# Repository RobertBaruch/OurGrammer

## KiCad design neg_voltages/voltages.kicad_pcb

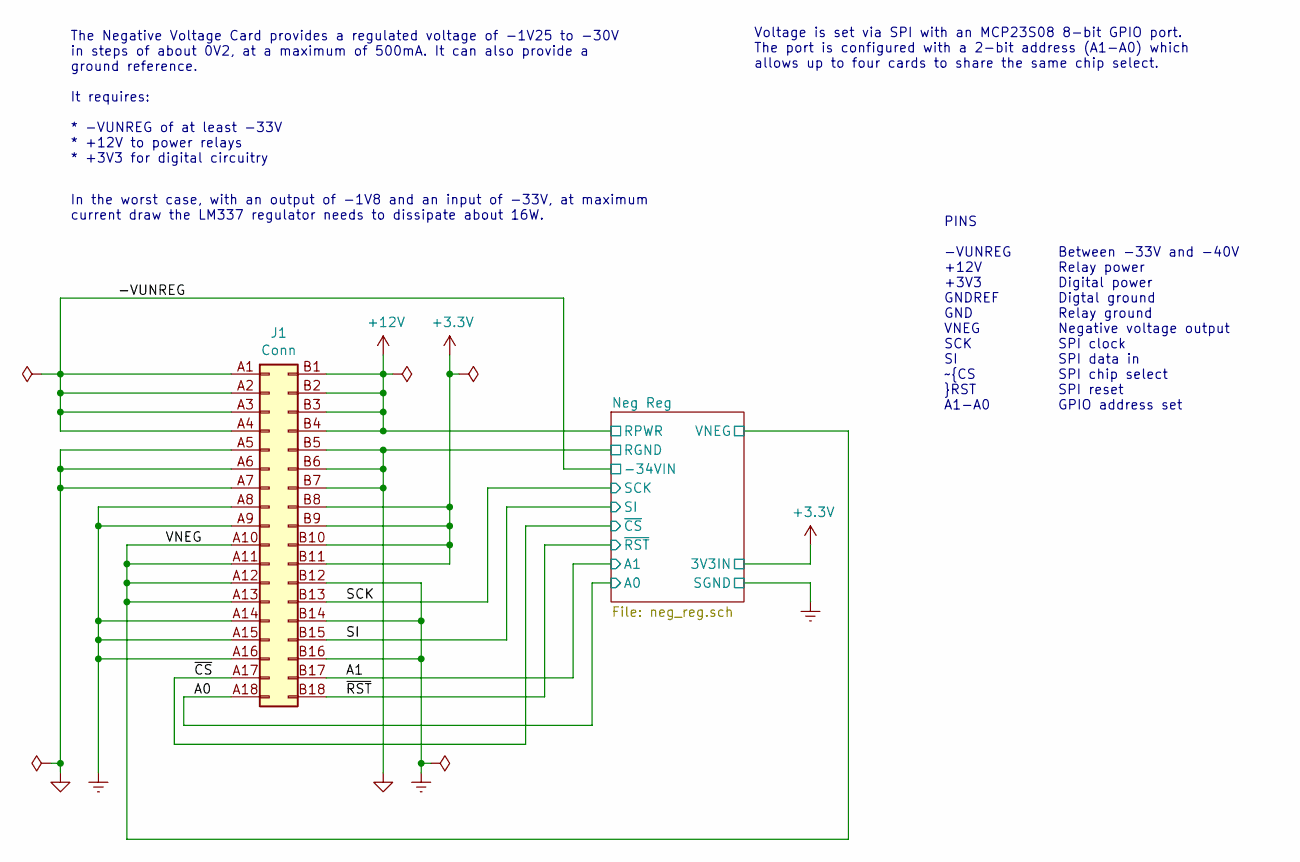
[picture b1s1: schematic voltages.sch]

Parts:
J1: Conn; BUS_PCIexpress_x1

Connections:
+3V3: J1.B8 (Pin_b8), J1.B9 (Pin_b9), J1.B10 (Pin_b10), J1.B11 (Pin_b11); also elsewhere on the board
+12V: J1.B1 (Pin_b1), J1.B2 (Pin_b2), J1.B3 (Pin_b3), J1.B4 (Pin_b4); also elsewhere on the board
/-VUNREG: J1.A1 (Pin_a1), J1.A2 (Pin_a2), J1.A3 (Pin_a3), J1.A4 (Pin_a4); also elsewhere on the board
/A0: J1.A18 (Pin_a18); also elsewhere on the board
/A1: J1.B17 (Pin_b17); also elsewhere on the board
/SCK: J1.B13 (Pin_b13); also elsewhere on the board
/SI: J1.B15 (Pin_b15); also elsewhere on the board
/VNEG: J1.A10 (Pin_a10), J1.A11 (Pin_a11), J1.A12 (Pin_a12), J1.A13 (Pin_a13); also elsewhere on the board
/~CS: J1.A17 (Pin_a17); also elsewhere on the board
/~RST: J1.B18 (Pin_b18); also elsewhere on the board
GND: J1.A5 (Pin_a5), J1.A6 (Pin_a6), J1.A7 (Pin_a7), J1.B5 (Pin_b5), J1.B6 (Pin_b6), J1.B7 (Pin_b7); also elsewhere on the board
GNDREF: J1.A8 (Pin_a8), J1.A9 (Pin_a9), J1.A14 (Pin_a14), J1.A15 (Pin_a15), J1.A16 (Pin_a16), J1.B12 (Pin_b12), J1.B14 (Pin_b14), J1.B16 (Pin_b16); also elsewhere on the board

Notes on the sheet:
The Negative Voltage Card provides a regulated voltage of -1V25 to -30V in steps of about 0V2, at a maximum of 500mA. It can also provide a ground reference. It requires: * -VUNREG of at least -33V * +12V to power relays * +3V3 for digital circuitry
In the worst case, with an output of -1V8 and an input of -33V, at maximum current draw the LM337 regulator needs to dissipate about 16W.
Voltage is set via SPI with an MCP23S08 8-bit GPIO port. The port is configured with a 2-bit address (A1-A0) which allows up to four cards to share the same chip select.
PINS -VUNREG +12V +3V3 GNDREF GND VNEG SCK SI ~CS ~RST A1-A0
Between -33V and -40V Relay power Digital power Digtal ground Relay ground Negative voltage output SPI clock SPI data in SPI chip select SPI reset GPIO address set

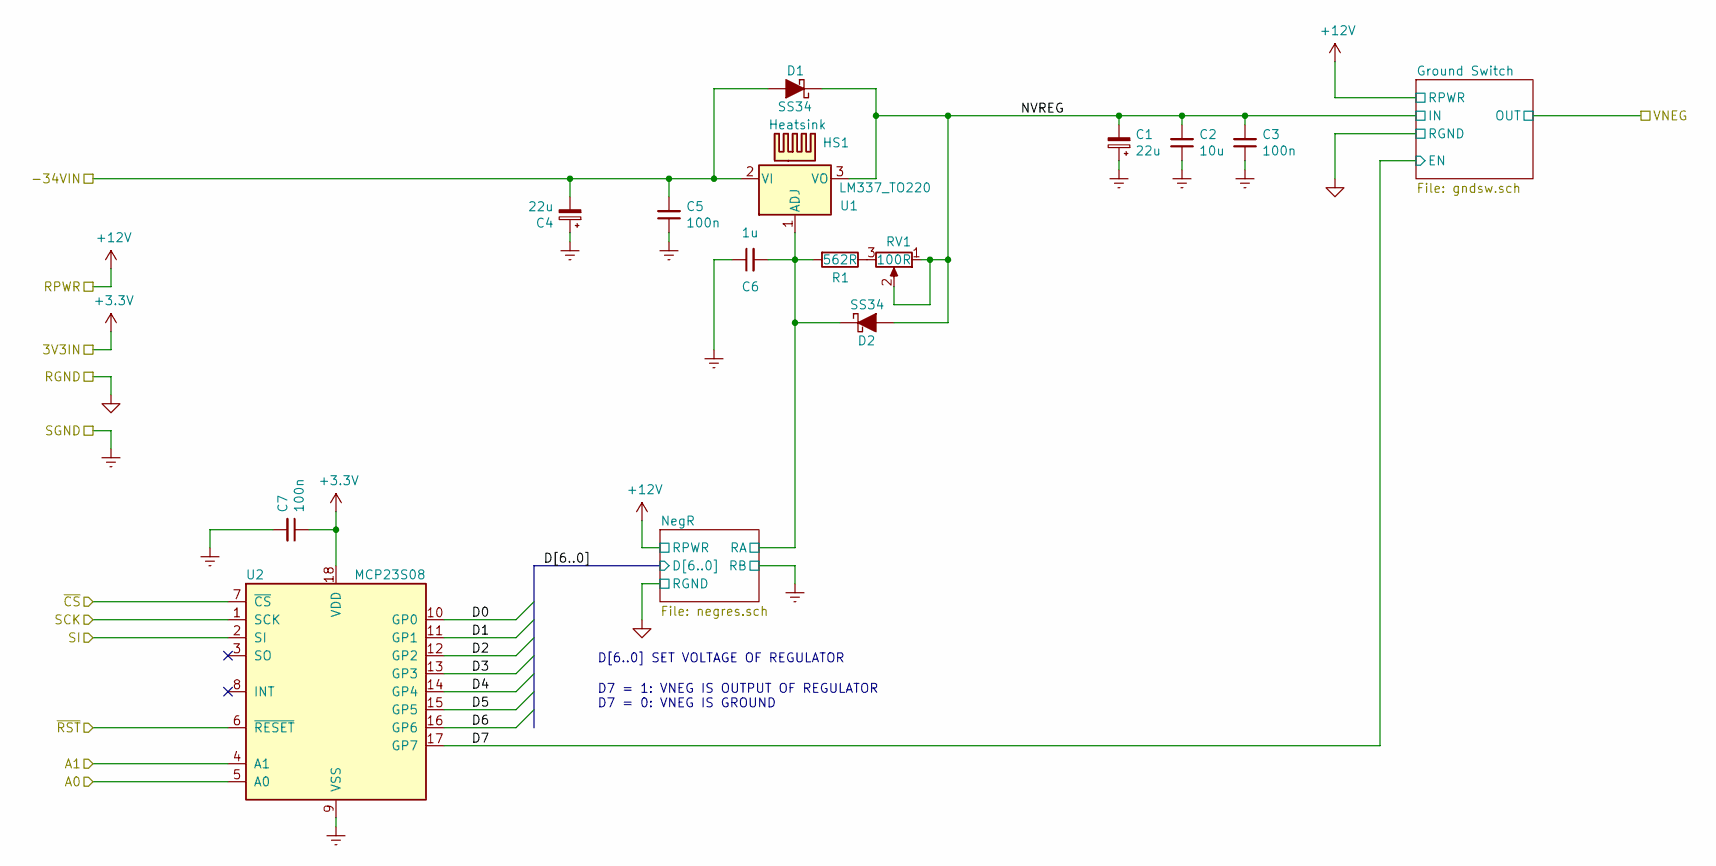
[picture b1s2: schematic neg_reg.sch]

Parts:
C1, C4: 22u; CP_Elec_6.3x7.7
C2: 10u; C_1206_3216Metric
C3, C5, C7: 100n; C_0805_2012Metric
C6: 1u; C_0805_2012Metric
D1, D2: SS34; D_SMA
HS1: Heatsink; Heatsink_22x10x25mm_1xFixation3mm
R1: 562R; R_0603_1608Metric
RV1: 100R; Potentiometer_Vishay_43_Horizontal
U1: LM337_TO220; TO-220-3_Horizontal_TabDown
U2: MCP23S08; SOIC-18W_7.5x11.6mm_P1.27mm

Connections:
+3V3: C7.1, U2.18 (VDD); also elsewhere on the board
/-VUNREG: C4.2, C5.2, D1.2 (A), U1.2 (VI); also elsewhere on the board
/A0: U2.5 (A0); also elsewhere on the board
/A1: U2.4 (A1); also elsewhere on the board
/Neg Reg/D0: U2.10 (GP0); also elsewhere on the board
/Neg Reg/D1: U2.11 (GP1); also elsewhere on the board
/Neg Reg/D2: U2.12 (GP2); also elsewhere on the board
/Neg Reg/D3: U2.13 (GP3); also elsewhere on the board
/Neg Reg/D4: U2.14 (GP4); also elsewhere on the board
/Neg Reg/D5: U2.15 (GP5); also elsewhere on the board
/Neg Reg/D6: U2.16 (GP6); also elsewhere on the board
/Neg Reg/D7: U2.17 (GP7); also elsewhere on the board
/Neg Reg/NVREG: C1.2, C2.2, C3.2, D1.1 (K), D2.2 (A), RV1.1, RV1.2, U1.3 (VO); also elsewhere on the board
/Neg Reg/NegR/RA: C6.2, D2.1 (K), R1.2, U1.1 (ADJ); also elsewhere on the board
/SCK: U2.1 (SCK); also elsewhere on the board
/SI: U2.2 (SI); also elsewhere on the board
/~CS: U2.7 (~CS); also elsewhere on the board
/~RST: U2.6 (~RESET); also elsewhere on the board
GNDREF: C1.1, C2.1, C3.1, C4.1, C5.1, C6.1, C7.2, U2.9 (VSS); also elsewhere on the board
unnamed: R1.1, RV1.3

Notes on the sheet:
D7 = 1: VNEG IS OUTPUT OF REGULATOR D7 = 0: VNEG IS GROUND
D[6..0] SET VOLTAGE OF REGULATOR

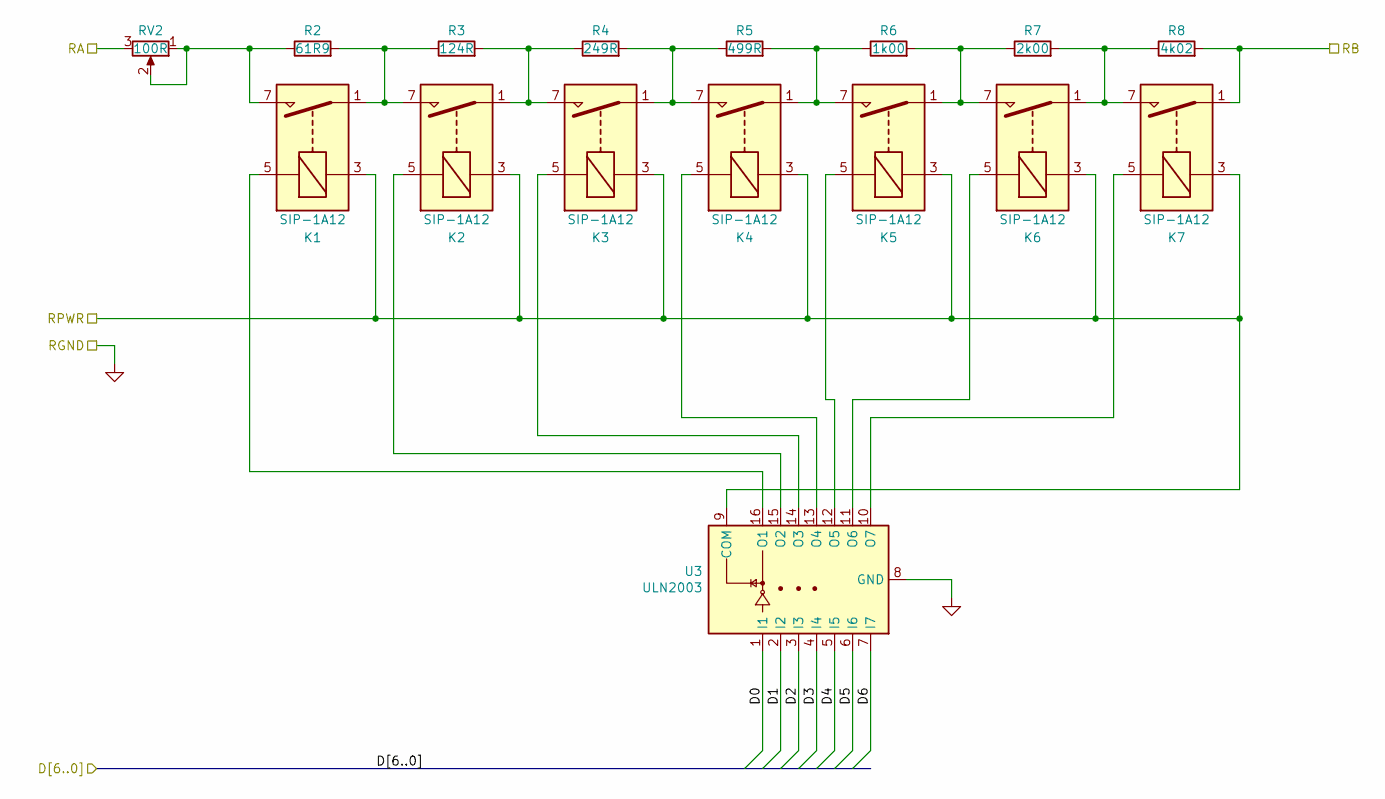
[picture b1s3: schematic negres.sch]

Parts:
K1, K2, K3, K4, K5, K6, K7: SIP-1A12; Relay_SPST_StandexMeder_SIL_Form1A
R2: 61R9; R_0603_1608Metric
R3: 124R; R_0603_1608Metric
R4: 249R; R_0603_1608Metric
R5: 499R; R_0603_1608Metric
R6: 1k00; R_0603_1608Metric
R7: 2k00; R_0603_1608Metric
R8: 4k02; R_0603_1608Metric
RV2: 100R; Potentiometer_Vishay_43_Horizontal
U3: ULN2003; SOP-16_4.4x10.4mm_P1.27mm

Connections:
+12V: K1.3, K2.3, K3.3, K4.3, K5.3, K6.3, K7.3, U3.9 (COM); also elsewhere on the board
/Neg Reg/D0: U3.1 (I1); also elsewhere on the board
/Neg Reg/D1: U3.2 (I2); also elsewhere on the board
/Neg Reg/D2: U3.3 (I3); also elsewhere on the board
/Neg Reg/D3: U3.4 (I4); also elsewhere on the board
/Neg Reg/D4: U3.5 (I5); also elsewhere on the board
/Neg Reg/D5: U3.6 (I6); also elsewhere on the board
/Neg Reg/D6: U3.7 (I7); also elsewhere on the board
/Neg Reg/NegR/RA: RV2.3; also elsewhere on the board
GND: U3.8 (GND); also elsewhere on the board
GNDREF: K7.1, R8.2; also elsewhere on the board
unnamed: K1.1, K2.7, R2.2, R3.1
unnamed: K1.5, U3.16 (O1)
unnamed: K1.7, R2.1, RV2.1, RV2.2
unnamed: K2.1, K3.7, R3.2, R4.1
unnamed: K2.5, U3.15 (O2)
unnamed: K3.1, K4.7, R4.2, R5.1
unnamed: K3.5, U3.14 (O3)
unnamed: K4.1, K5.7, R5.2, R6.1
unnamed: K4.5, U3.13 (O4)
unnamed: K5.1, K6.7, R6.2, R7.1
unnamed: K5.5, U3.12 (O5)
unnamed: K6.1, K7.7, R7.2, R8.1
unnamed: K6.5, U3.11 (O6)
unnamed: K7.5, U3.10 (O7)

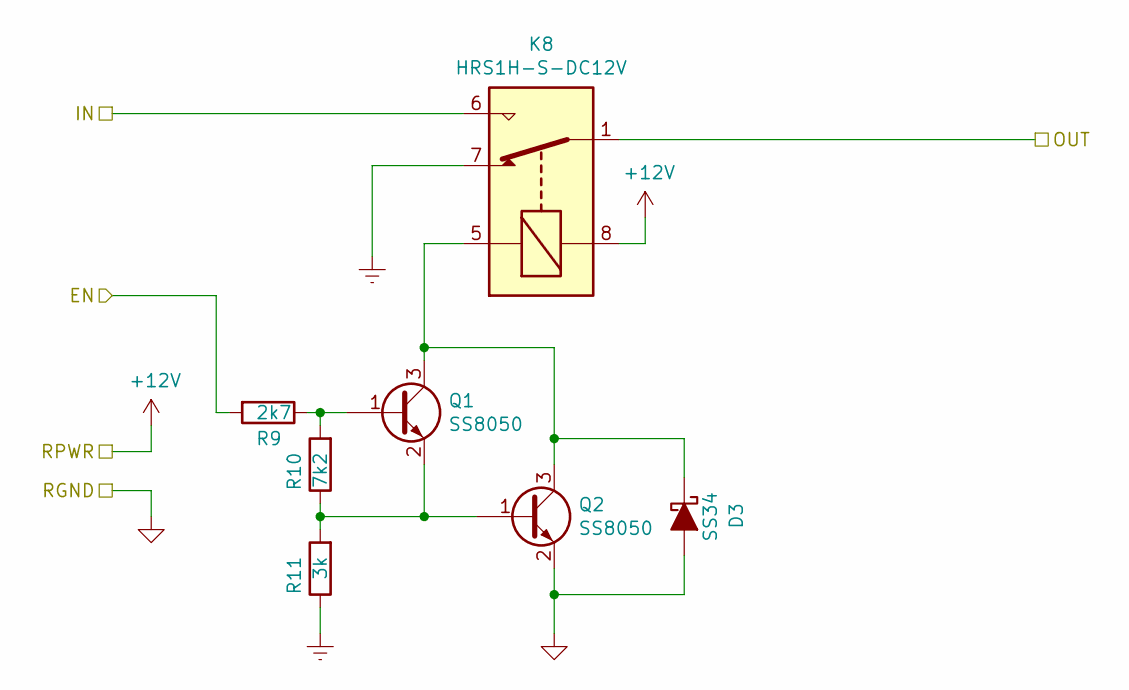
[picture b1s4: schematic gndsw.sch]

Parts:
D3: SS34; D_SMA
K8: HRS1H-S-DC12V; Relay_SPDT_HJR-4102
Q1, Q2: SS8050; SOT-23
R9: 2k7; R_0603_1608Metric
R10: 7k2; R_0603_1608Metric
R11: 3k; R_0603_1608Metric

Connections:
+12V: K8.8 (C2); also elsewhere on the board
/Neg Reg/D7: R9.2; also elsewhere on the board
/Neg Reg/NVREG: K8.6 (NO); also elsewhere on the board
/VNEG: K8.1 (COM), K8.12; also elsewhere on the board
GND: D3.2 (A), Q2.2 (E); also elsewhere on the board
GNDREF: K8.7 (NC), R11.1; also elsewhere on the board
unnamed: D3.1 (K), K8.5 (C1), Q1.3 (C), Q2.3 (C)
unnamed: Q1.1 (B), R9.1, R10.2
unnamed: Q1.2 (E), Q2.1 (B), R10.1, R11.2

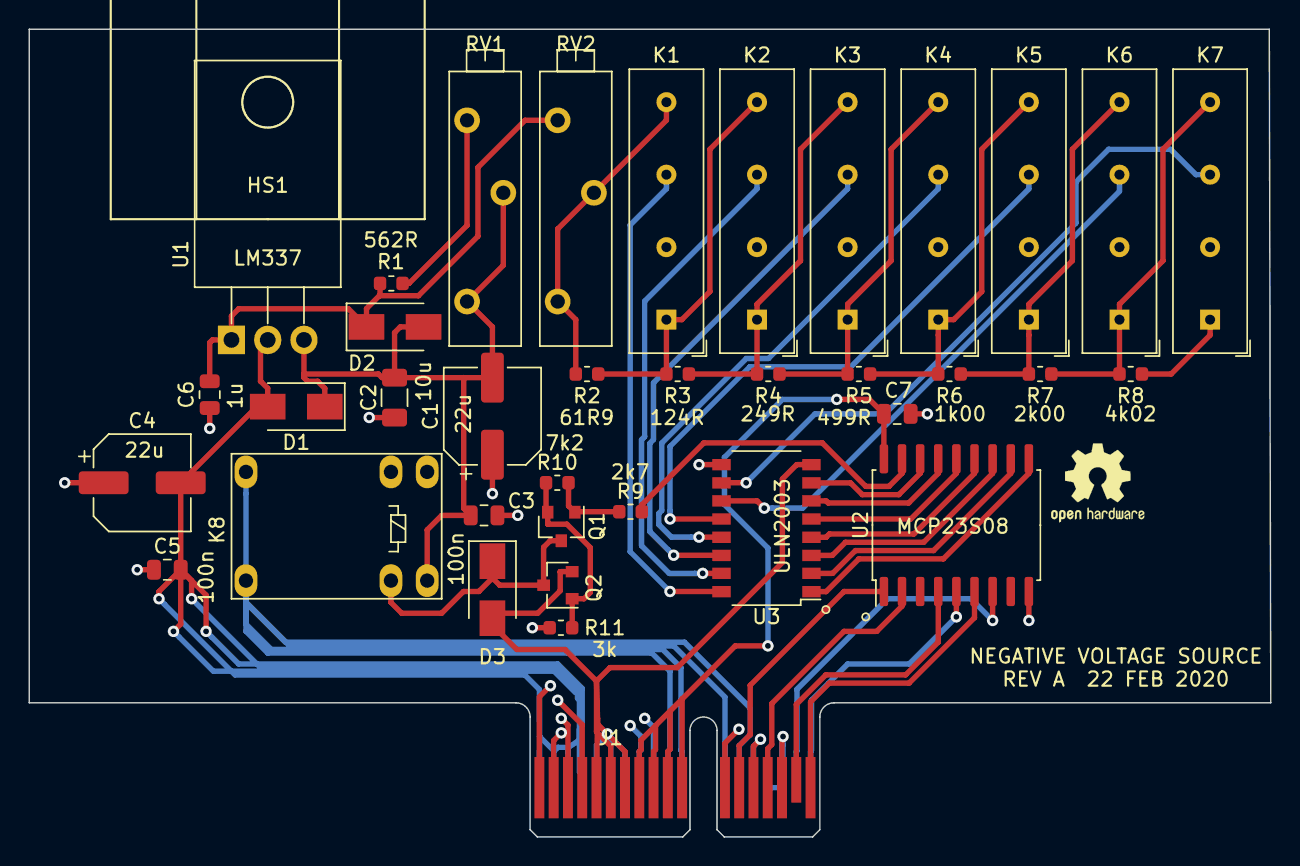
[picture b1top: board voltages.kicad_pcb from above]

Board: 4 copper layers, 87.0 x 56.6 mm, 38 parts (0 on the bottom side), 40 nets.

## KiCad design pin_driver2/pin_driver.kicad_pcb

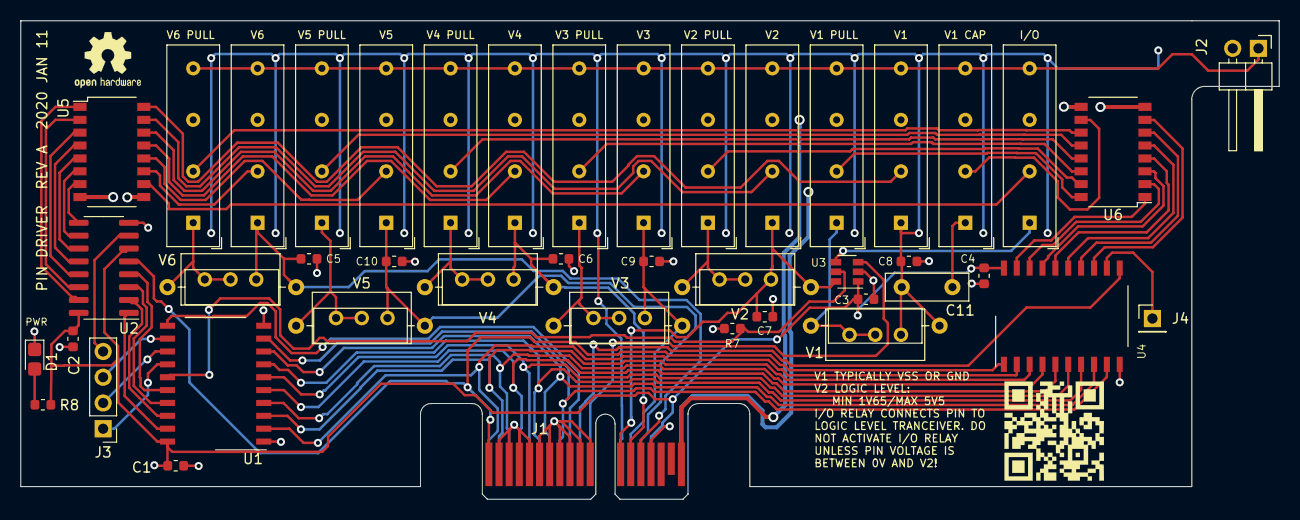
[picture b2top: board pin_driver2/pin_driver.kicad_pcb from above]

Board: 4 copper layers, 124.2 x 47.2 mm, 51 parts (0 on the bottom side), 70 nets.

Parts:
C1, C2, C3, C4, C5, C6, C7, C8, C9, C10: 100n; C_0603_1608Metric
C11: 100n; C_Disc_D8.0mm_W2.5mm_P5.00mm
D1: LED_PWR; LED_0805_2012Metric_Castellated
J1: Conn_02x18_Row_CapLetter_First; BUS_PCIexpress_x1
J2: Conn_02x01; PinHeader_1x02_P2.54mm_Horizontal
J3: Conn_01x04; PinHeader_1x04_P2.54mm_Vertical
J4: Conn_01x01; PinHeader_1x01_P2.54mm_Vertical
K1, K2, K3, K4, K5, K6, K7, K8, K9, K10, K11, K12, K13, K14: SILxx-1Axx-71x; Relay_SPST_StandexMeder_SIL_Form1A
R1, R2, R3, R4, R5, R6: 1k; R_Axial_DIN0309_L9.0mm_D3.2mm_P12.70mm_Horizontal
R7, R8: 1k; R_0603_1608Metric
RV1, RV2, RV3, RV4, RV5, RV6: 47k; Potentiometer_Bourns_3296W_Vertical
Ref**: Val**; rickroll_qr
U1, U4: 74HCT574; SO-20_12.8x7.5mm_P1.27mm
U2: 74HC237; SOIC-16_3.9x9.9mm_P1.27mm
U3: SN74LVC1T45DBV; SOT-23-6
U5, U6: ULN2003A; SOP-16_4.4x10.4mm_P1.27mm

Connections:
+3V3: C1.1, C2.1, C3.1, C4.1, J1.A15, R8.2, U1.20, U2.6, U2.16, U3.1, U4.20
/D0: J1.A1, U1.2, U4.2
/D1: J1.A2, U1.3, U4.3
/D2: J1.A3, U1.4, U4.4
/D3: J1.A4, U1.5, U4.5
/D4: J1.A5, U1.6, U4.6
/D5: J1.A6, U1.7, U4.7
/D6: J1.A7, U1.8, U4.8
/D7: J1.A8, U1.9, U4.9
/IO: J1.A11, U3.3
/IO_PIN_DIR: R7.2, U1.15, U3.5
/PIN: J2.1, K1.7, K2.7, K3.7, K4.7, K5.7, K6.7, K7.7, K8.7, K9.7, K10.7, K11.7, K12.7, K13.7, K14.7
/PULL1: K8.1, R1.1, RV1.1, RV1.2
/PULL2: K9.1, R2.1, RV2.1, RV2.2
/PULL3: K10.1, R3.1, RV3.1, RV3.2
/PULL4: K11.1, R4.1, RV4.1, RV4.2
/PULL5: K12.1, R5.1, RV5.1, RV5.2
/PULL6: K13.1, R6.1, RV6.1, RV6.2
/PULL7: C11.1, K14.1
/R1CLK: J1.A9, U1.11
/R1_SEL5: J3.1, U1.14
/R1_SEL6: J3.2, U1.13
/R1_SEL7: J3.3, U1.12
/R1_V1: U2.15, U5.1
/R1_V2: U2.14, U5.2
/R1_V3: U2.13, U5.3
/R1_V4: U2.12, U5.4
/R1_V5: U2.11, U5.5
/R1_V6: U2.10, U5.6
/R1_V7: U2.9, U5.7
/R1_V8: J3.4, U2.7
/R2CLK: J1.A10, U4.11
/R2_V1: U4.19, U6.1
/R2_V2: U4.18, U6.2
/R2_V3: U4.17, U6.3
/R2_V4: U4.16, U6.4
/R2_V5: U4.15, U6.5
/R2_V6: U4.14, U6.6
/R2_V7: U4.13, U6.7
/R2_V8: J4.1, U4.12
/V1: C8.1, C11.2, J1.A12, J2.2, K1.1, R1.2, RV1.3
/V2: C7.1, J1.B12, K2.1, R2.2, RV2.3, U3.6
/V3: C9.1, J1.A13, K3.1, R3.2, RV3.3
/V4: C6.1, J1.B13, K4.1, R4.2, RV4.3
/V5: C10.1, J1.A14, K5.1, R5.2, RV5.3
/V6: C5.1, J1.B14, K6.1, R6.2, RV6.3
/V7: K7.1, U3.4
/VRELAY: J1.B18, K1.5, K2.5, K3.5, K4.5, K5.5, K6.5, K7.5, K8.5, K9.5, K10.5, K11.5, K12.5, K13.5, K14.5, U5.9, U6.9
/VRELAY_RTN: J1.A18, U5.8, U6.8
/~OE: J1.B1, U2.5, U4.1
GNDREF: C1.2, C2.2, C3.2, C4.2, C5.2, C6.2, C7.2, C8.2, C9.2, C10.2, D1.1, J1.B2, J1.B3, J1.B4, J1.B5, J1.B6, J1.B7, J1.B8, J1.B9, J1.B10, J1.B11, J1.B15, R7.1, U1.1, U1.10, U2.8, U3.2, U4.10
unnamed: D1.2, R8.1
unnamed: K1.3, U5.16
unnamed: K2.3, U5.15
unnamed: K3.3, U5.14
unnamed: K4.3, U5.13
unnamed: K5.3, U5.12
unnamed: K6.3, U5.11
unnamed: K7.3, U5.10
unnamed: K8.3, U6.16
unnamed: K9.3, U6.15
unnamed: K10.3, U6.14
unnamed: K11.3, U6.13
unnamed: K12.3, U6.12
unnamed: K13.3, U6.11
unnamed: K14.3, U6.10
unnamed: U1.16, U2.4
unnamed: U1.17, U2.3
unnamed: U1.18, U2.2
unnamed: U1.19, U2.1

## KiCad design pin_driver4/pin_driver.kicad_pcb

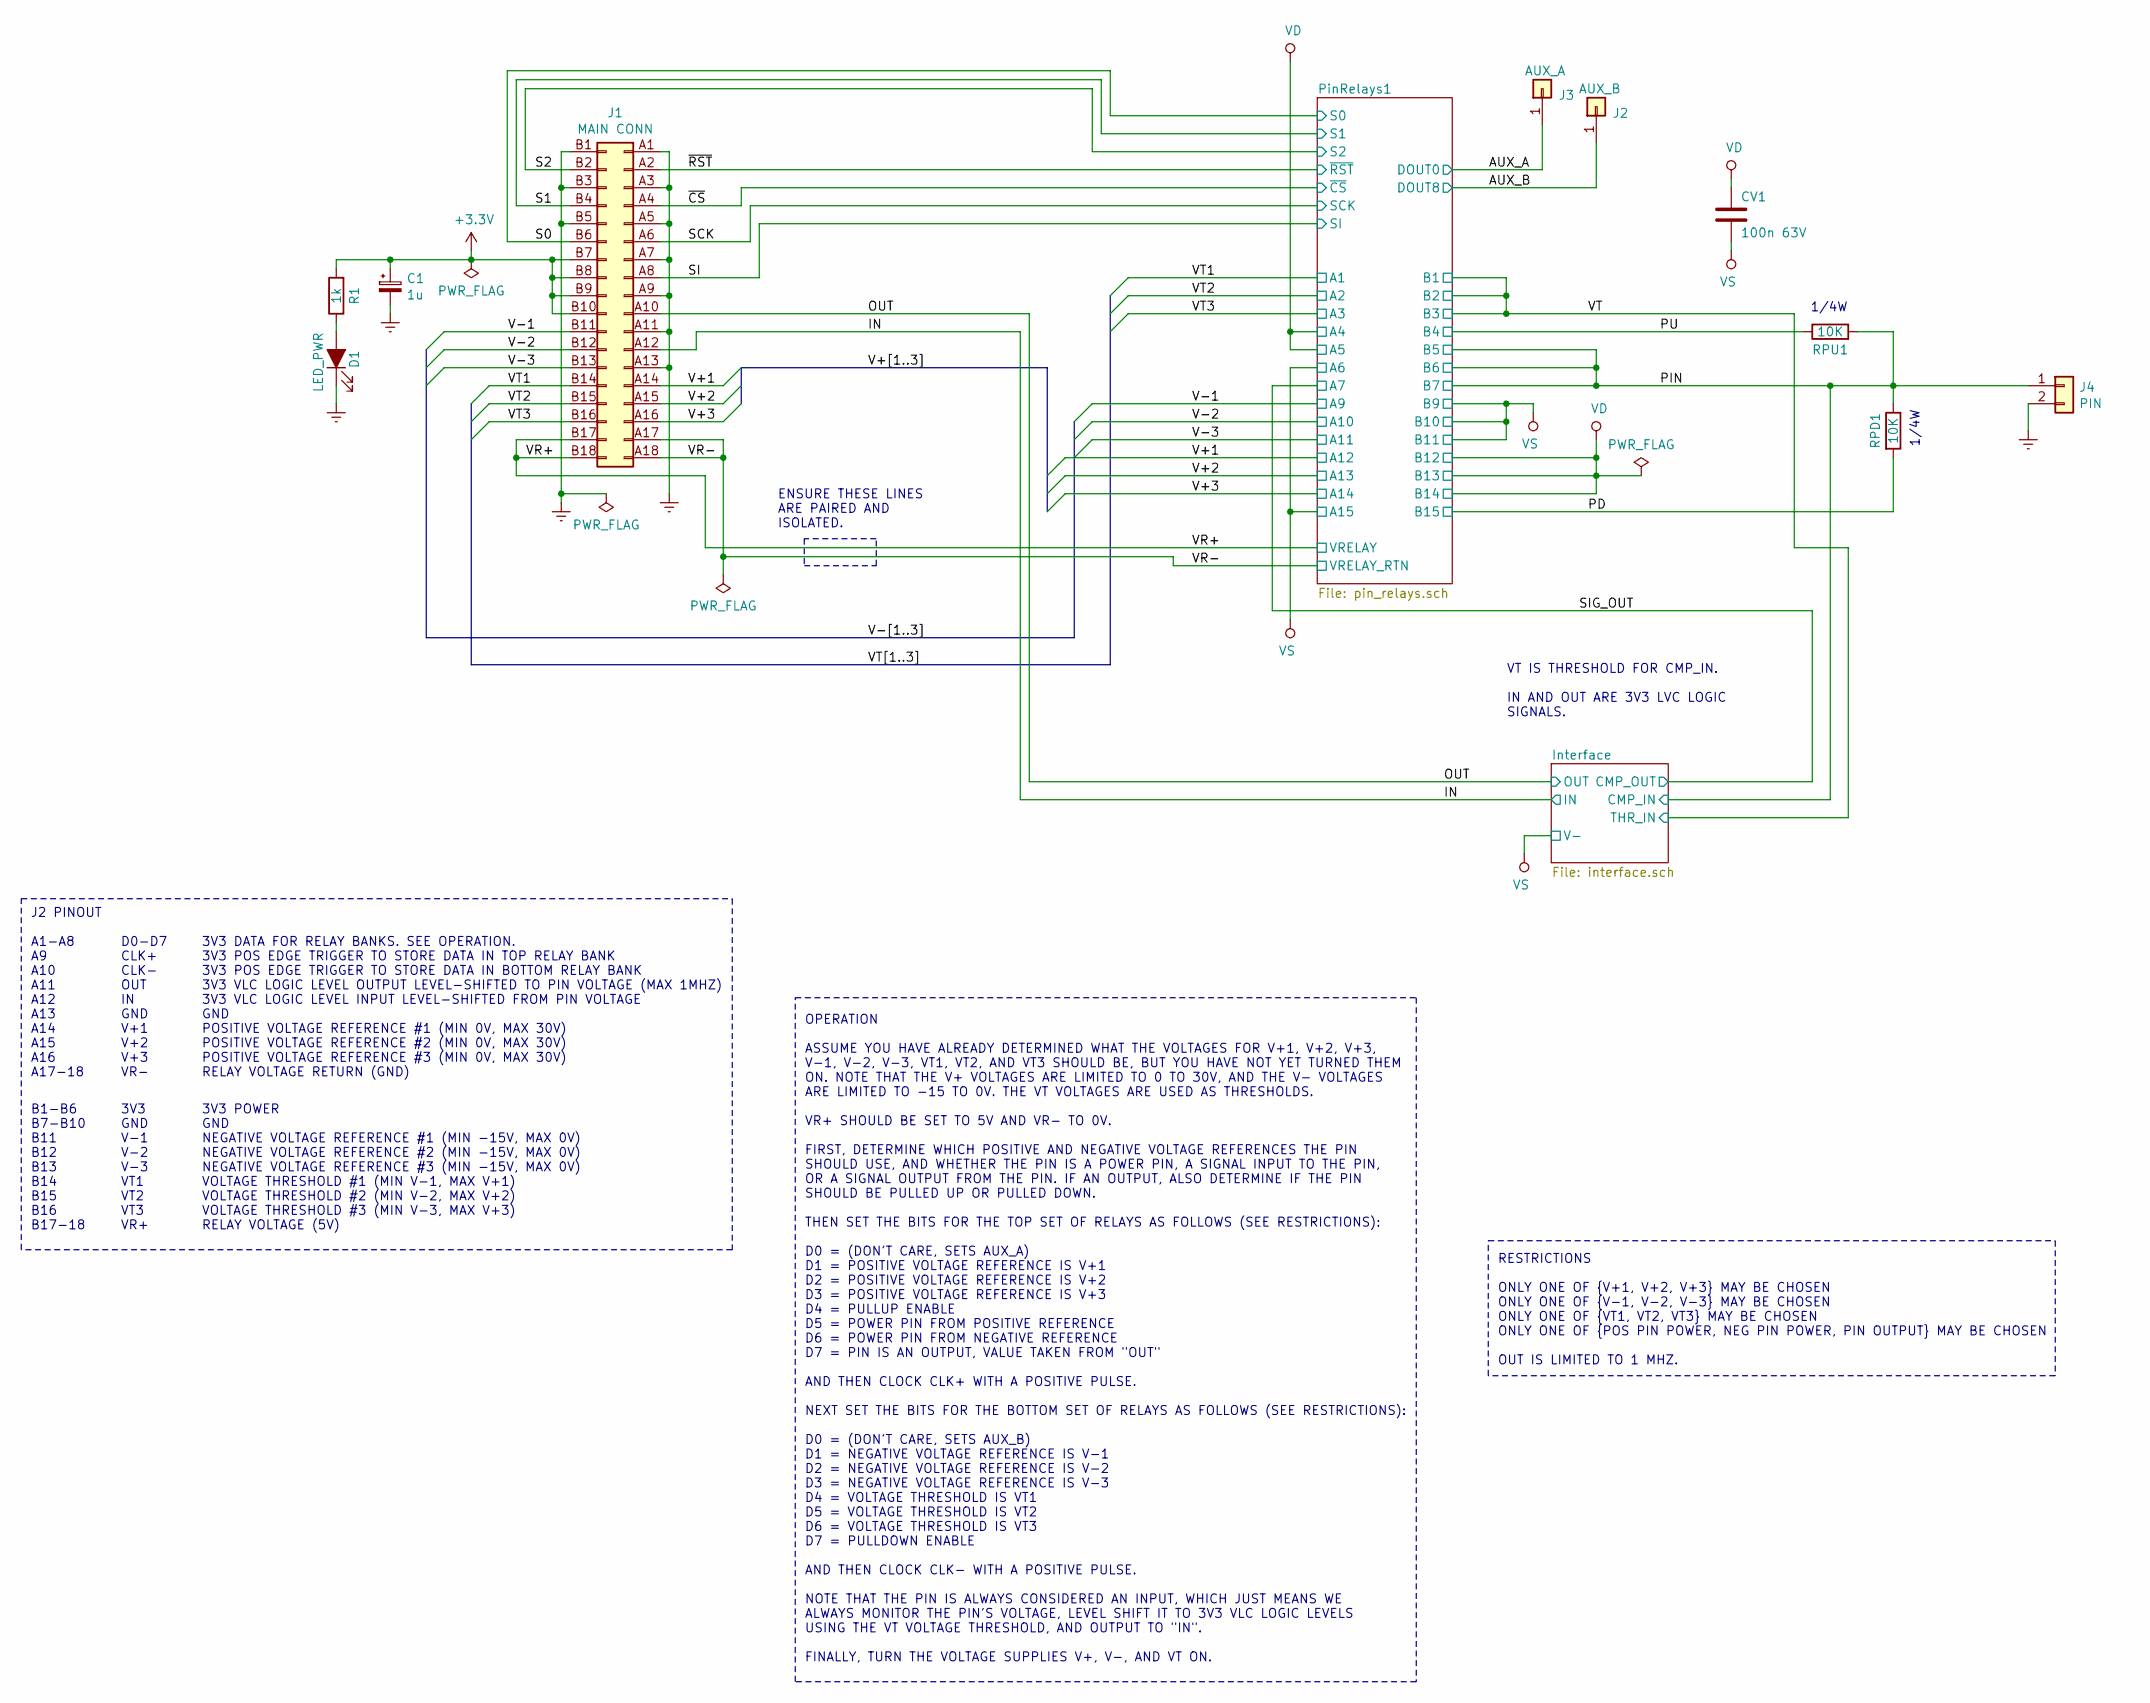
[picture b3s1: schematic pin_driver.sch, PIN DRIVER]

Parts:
C1: 1u; CP_Elec_4x5.4
CV1: 100n 63V; C_0805_2012Metric
D1: LED_PWR; LED_0805_2012Metric_Castellated
J1: MAIN CONN; BUS_PCIexpress_x1
J2: AUX_B; PinHeader_1x01_P2.54mm_Vertical
J3: AUX_A; PinHeader_1x01_P2.54mm_Vertical
J4: PIN; PinHeader_1x02_P2.54mm_Horizontal
R1: 1k; R_0603_1608Metric
RPD1: 10K; R_1206_3216Metric
RPU1: 10K; R_1206_3216Metric

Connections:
+3V3: C1.1, J1.B7 (Pin_b7), J1.B8 (Pin_b8), J1.B9 (Pin_b9), J1.B10 (Pin_b10), R1.2; also elsewhere on the board
/AUX_A: J3.1; also elsewhere on the board
/AUX_B: J2.1; also elsewhere on the board
/IN: J1.A12 (Pin_a12); also elsewhere on the board
/OUT: J1.A10 (Pin_a10); also elsewhere on the board
/PD: RPD1.2; also elsewhere on the board
/PIN: J4.1, RPD1.1, RPU1.2; also elsewhere on the board
/PU: RPU1.1; also elsewhere on the board
/S0: J1.B6 (Pin_b6); also elsewhere on the board
/S1: J1.B4 (Pin_b4); also elsewhere on the board
/S2: J1.B2 (Pin_b2); also elsewhere on the board
/SCK: J1.A6 (Pin_a6); also elsewhere on the board
/SI: J1.A8 (Pin_a8); also elsewhere on the board
/V+1: J1.A14 (Pin_a14); also elsewhere on the board
/V+2: J1.A15 (Pin_a15); also elsewhere on the board
/V+3: J1.A16 (Pin_a16); also elsewhere on the board
/V-1: J1.B11 (Pin_b11); also elsewhere on the board
/V-2: J1.B12 (Pin_b12); also elsewhere on the board
/V-3: J1.B13 (Pin_b13); also elsewhere on the board
/VR+: J1.B17 (Pin_b17), J1.B18 (Pin_b18); also elsewhere on the board
/VR-: J1.A17 (Pin_a17), J1.A18 (Pin_a18); also elsewhere on the board
/VT1: J1.B14 (Pin_b14); also elsewhere on the board
/VT2: J1.B15 (Pin_b15); also elsewhere on the board
/VT3: J1.B16 (Pin_b16); also elsewhere on the board
/~CS: J1.A4 (Pin_a4); also elsewhere on the board
/~RST: J1.A2 (Pin_a2); also elsewhere on the board
GNDREF: C1.2, D1.1 (K), J1.A1 (Pin_a1), J1.A3 (Pin_a3), J1.A5 (Pin_a5), J1.A7 (Pin_a7), J1.A9 (Pin_a9), J1.A11 (Pin_a11), J1.A13 (Pin_a13), J1.B1 (Pin_b1), J1.B3 (Pin_b3), J1.B5 (Pin_b5), J4.2; also elsewhere on the board
unnamed: D1.2 (A), R1.1
VD: CV1.1; also elsewhere on the board
VS: CV1.2; also elsewhere on the board

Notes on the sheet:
1/4W
ENSURE THESE LINES ARE PAIRED AND ISOLATED.
VT IS THRESHOLD FOR CMP_IN. IN AND OUT ARE 3V3 LVC LOGIC SIGNALS.
RESTRICTIONS ONLY ONE OF {V+1, V+2, V+3} MAY BE CHOSEN ONLY ONE OF {V-1, V-2, V-3} MAY BE CHOSEN ONLY ONE OF {VT1, VT2, VT3} MAY BE CHOSEN ONLY ONE OF {POS PIN POWER, NEG PIN POWER, PIN OUTPUT} MAY BE CHOSEN OUT IS LIMITED TO 1 MHZ.
OPERATION ASSUME YOU HAVE ALREADY DETERMINED WHAT THE VOLTAGES FOR V+1, V+2, V+3, V-1, V-2, V-3, VT1, VT2, AND VT3 SHOULD BE, BUT YOU HAVE NOT YET TURNED THEM ON. NOTE THAT THE V+ VOLTAGES ARE LIMITED TO 0 TO 30V, AND THE V- VOLTAGES ARE LIMITED TO -15 TO 0V. THE VT VOLTAGES ARE USED AS THRESHOLDS.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
J2 PINOUT A1-A8 A9 A10 A11 A12 A13 A14 A15 A16 A17-18
D0-D7 CLK+ CLK- OUT IN GND V+1 V+2 V+3 VR-
3V3 DATA FOR RELAY BANKS. SEE OPERATION. 3V3 POS EDGE TRIGGER TO STORE DATA IN TOP RELAY BANK 3V3 POS EDGE TRIGGER TO STORE DATA IN BOTTOM RELAY BANK 3V3 VLC LOGIC LEVEL OUTPUT LEVEL-SHIFTED TO PIN VOLTAGE (MAX 1MHZ) 3V3 VLC LOGIC LEVEL INPUT LEVEL-SHIFTED FROM PIN VOLTAGE GND POSITIVE VOLTAGE REFE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
B1-B6 B7-B10 B11 B12 B13 B14 B15 B16 B17-18
3V3 GND V-1 V-2 V-3 VT1 VT2 VT3 VR+
3V3 POWER GND NEGATIVE VOLTAGE REFERENCE #1 (MIN -15V, MAX 0V) NEGATIVE VOLTAGE REFERENCE #2 (MIN -15V, MAX 0V) NEGATIVE VOLTAGE REFERENCE #3 (MIN -15V, MAX 0V) VOLTAGE THRESHOLD #1 (MIN V-1, MAX V+1) VOLTAGE THRESHOLD #2 (MIN V-2, MAX V+2) VOLTAGE THRESHOLD #3 (MIN V-3, MAX V+3) RELAY VOLTAGE (5V)

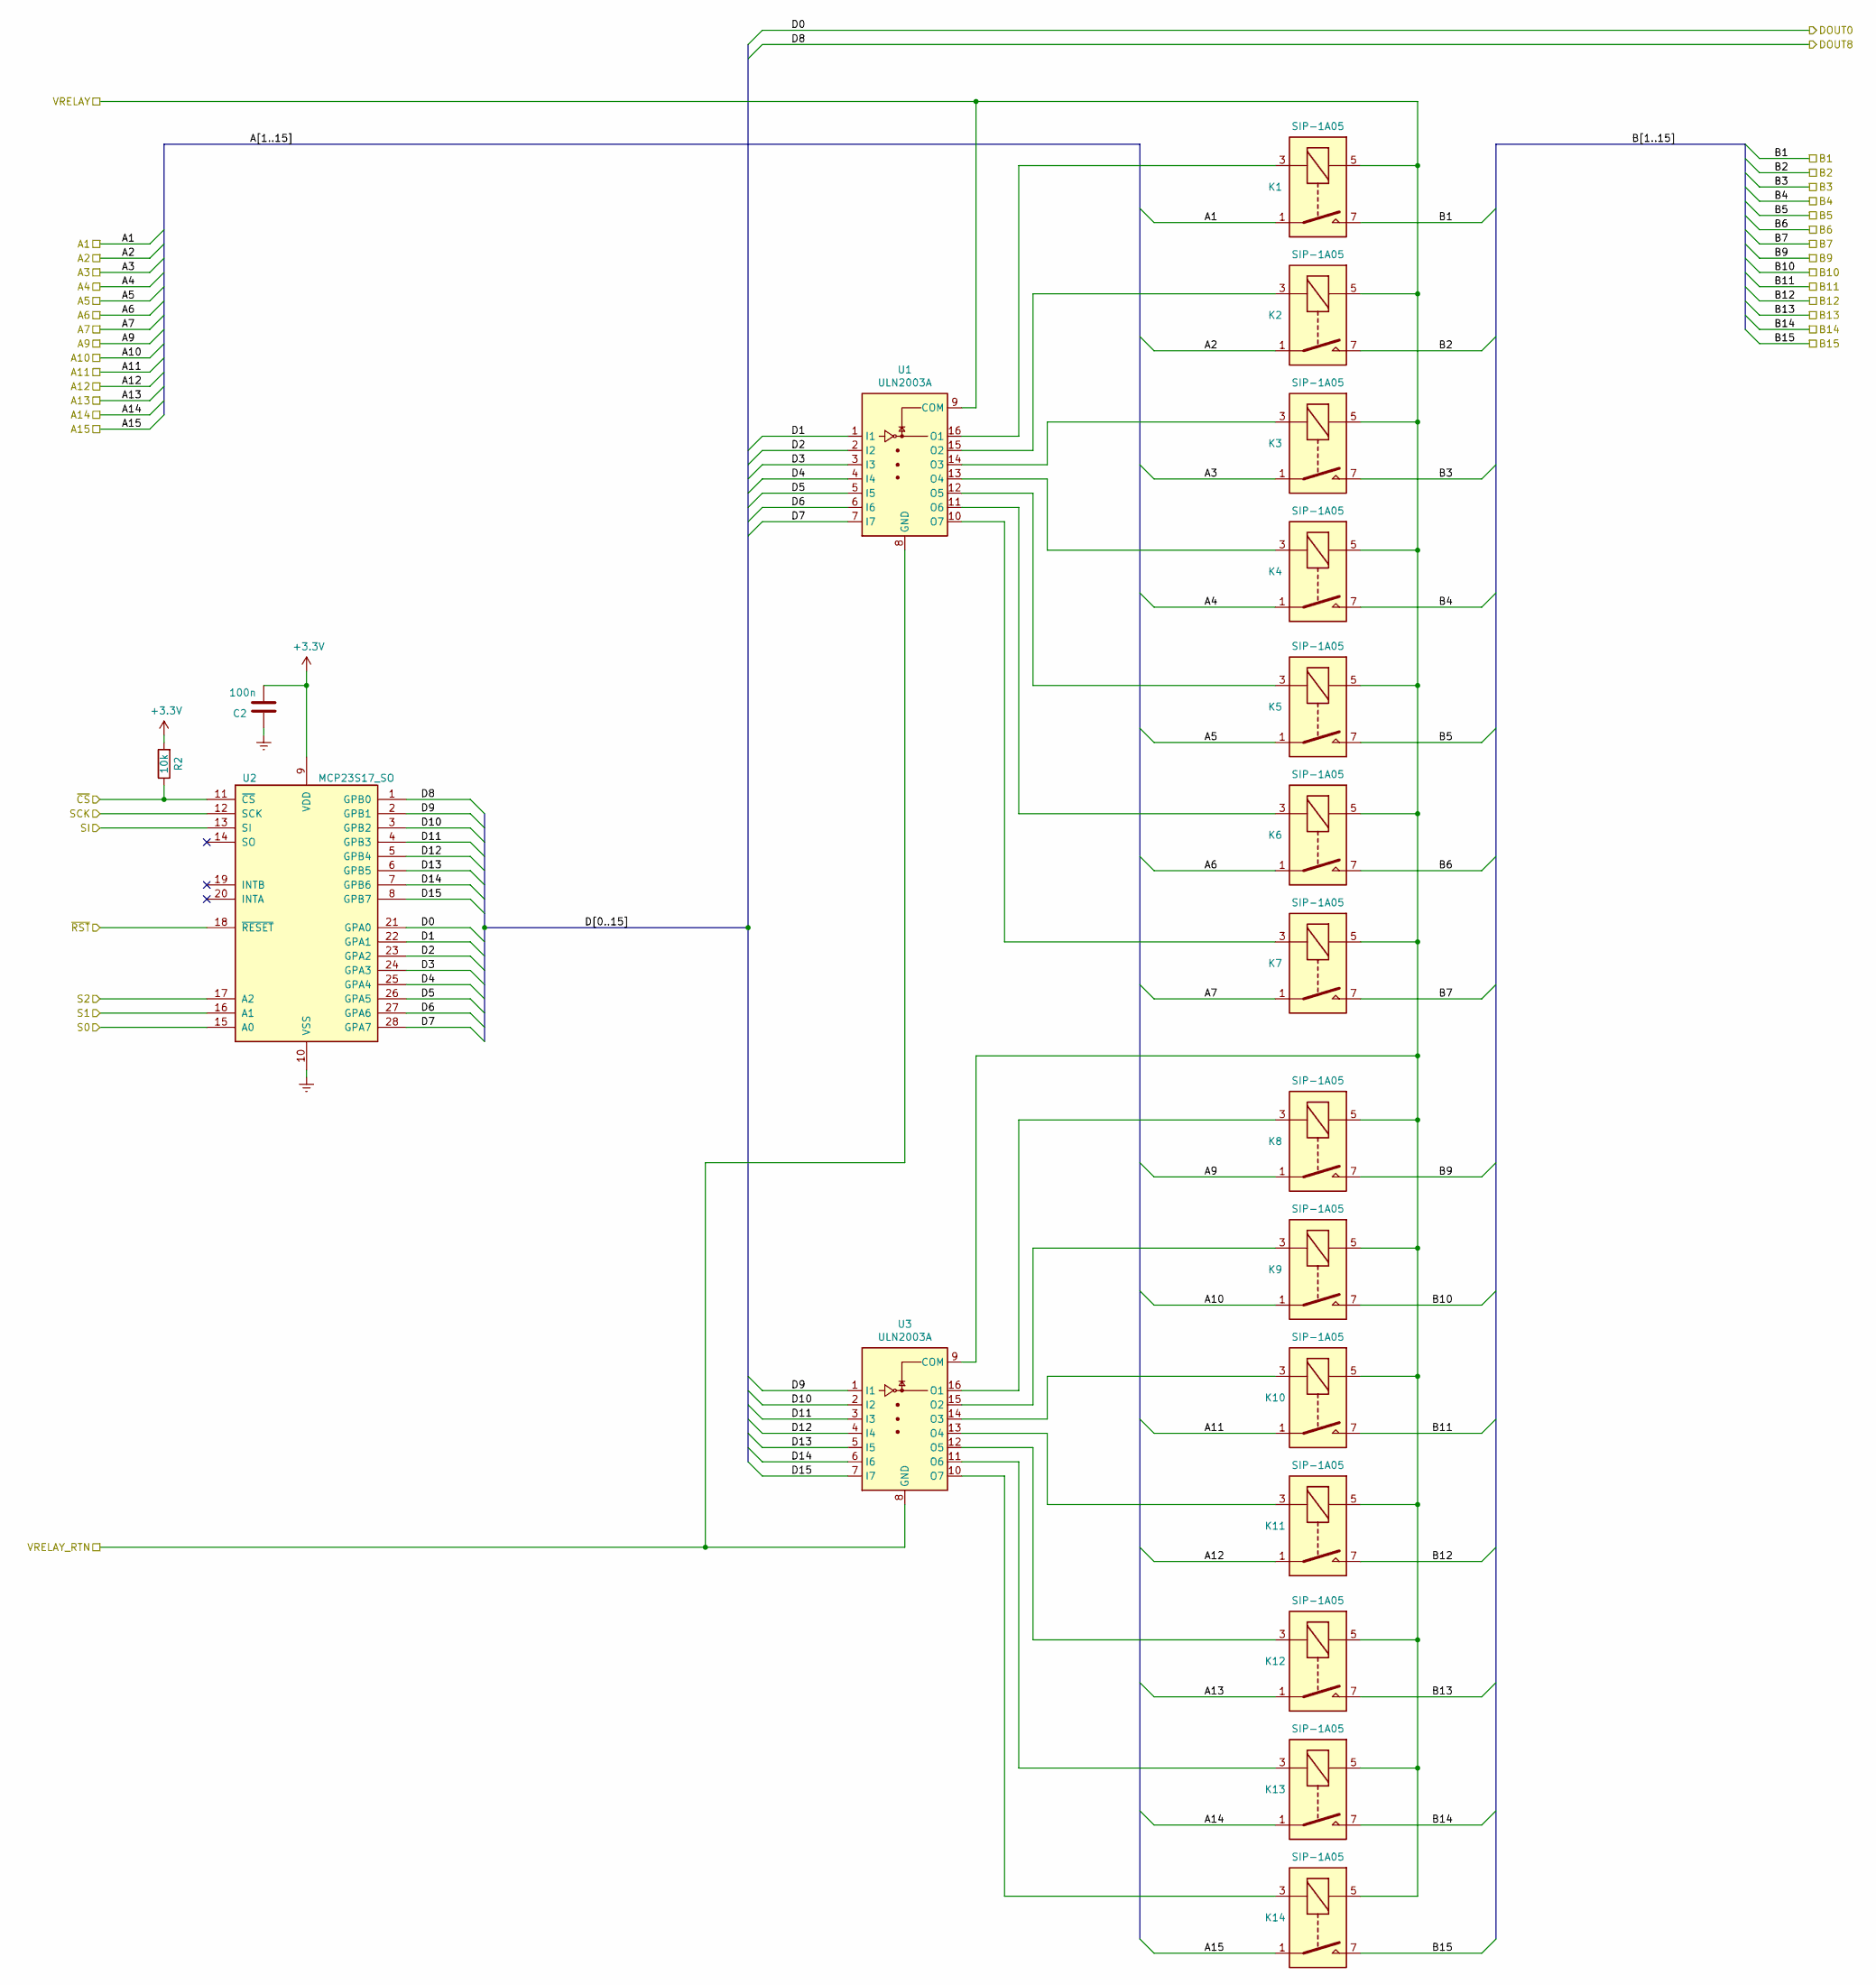
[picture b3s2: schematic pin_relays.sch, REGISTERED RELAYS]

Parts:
C2: 100n; C_0603_1608Metric
K1, K2, K3, K4, K5, K6, K7, K8, K9, K10, K11, K12, K13, K14: SIP-1A05; Relay_SPST_StandexMeder_SIL_Form1A
R2: 10k; R_0603_1608Metric
U1, U3: ULN2003A; SOP-16_4.4x10.4mm_P1.27mm
U2: MCP23S17_SO; SOIC-28W_7.5x17.9mm_P1.27mm

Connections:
+3V3: C2.2, R2.2, U2.9 (VDD); also elsewhere on the board
/AUX_A: U2.21 (GPA0); also elsewhere on the board
/AUX_B: U2.1 (GPB0); also elsewhere on the board
/PD: K14.7; also elsewhere on the board
/PIN: K5.7, K6.7, K7.7; also elsewhere on the board
/PU: K4.7; also elsewhere on the board
/PinRelays1/D1: U1.1 (I1), U2.22 (GPA1)
/PinRelays1/D2: U1.2 (I2), U2.23 (GPA2)
/PinRelays1/D3: U1.3 (I3), U2.24 (GPA3)
/PinRelays1/D4: U1.4 (I4), U2.25 (GPA4)
/PinRelays1/D5: U1.5 (I5), U2.26 (GPA5)
/PinRelays1/D6: U1.6 (I6), U2.27 (GPA6)
/PinRelays1/D7: U1.7 (I7), U2.28 (GPA7)
/PinRelays1/D9: U2.2 (GPB1), U3.1 (I1)
/PinRelays1/D10: U2.3 (GPB2), U3.2 (I2)
/PinRelays1/D11: U2.4 (GPB3), U3.3 (I3)
/PinRelays1/D12: U2.5 (GPB4), U3.4 (I4)
/PinRelays1/D13: U2.6 (GPB5), U3.5 (I5)
/PinRelays1/D14: U2.7 (GPB6), U3.6 (I6)
/PinRelays1/D15: U2.8 (GPB7), U3.7 (I7)
/S0: U2.15 (A0); also elsewhere on the board
/S1: U2.16 (A1); also elsewhere on the board
/S2: U2.17 (A2); also elsewhere on the board
/SCK: U2.12 (SCK); also elsewhere on the board
/SI: U2.13 (SI); also elsewhere on the board
/SIG_OUT: K7.1; also elsewhere on the board
/V+1: K11.1; also elsewhere on the board
/V+2: K12.1; also elsewhere on the board
/V+3: K13.1; also elsewhere on the board
/V-1: K8.1; also elsewhere on the board
/V-2: K9.1; also elsewhere on the board
/V-3: K10.1; also elsewhere on the board
/VR+: K1.5, K2.5, K3.5, K4.5, K5.5, K6.5, K7.5, K8.5, K9.5, K10.5, K11.5, K12.5, K13.5, K14.5, U1.9 (COM), U3.9 (COM); also elsewhere on the board
/VR-: U1.8 (GND), U3.8 (GND); also elsewhere on the board
/VT: K1.7, K2.7, K3.7; also elsewhere on the board
/VT1: K1.1; also elsewhere on the board
/VT2: K2.1; also elsewhere on the board
/VT3: K3.1; also elsewhere on the board
/~CS: R2.1, U2.11 (~CS~); also elsewhere on the board
/~RST: U2.18 (~RESET~); also elsewhere on the board
GNDREF: C2.1, U2.10 (VSS); also elsewhere on the board
unnamed: K1.3, U1.16 (O1)
unnamed: K2.3, U1.15 (O2)
unnamed: K3.3, U1.14 (O3)
unnamed: K4.3, U1.13 (O4)
unnamed: K5.3, U1.12 (O5)
unnamed: K6.3, U1.11 (O6)
unnamed: K7.3, U1.10 (O7)
unnamed: K8.3, U3.16 (O1)
unnamed: K9.3, U3.15 (O2)
unnamed: K10.3, U3.14 (O3)
unnamed: K11.3, U3.13 (O4)
unnamed: K12.3, U3.12 (O5)
unnamed: K13.3, U3.11 (O6)
unnamed: K14.3, U3.10 (O7)
VD: K4.1, K5.1, K11.7, K12.7, K13.7; also elsewhere on the board
VS: K6.1, K8.7, K9.7, K10.7, K14.1; also elsewhere on the board
